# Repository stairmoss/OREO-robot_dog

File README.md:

# OREO – ROS Based Quadruped Robot Dog

# OREO V2 – ROS Powered Vision-Based Quadruped Robot  
### Hack Club Advanced Robotics Project

OREO V2 is a next-generation quadruped robot dog powered by a Raspberry Pi 4 and Teensy microcontroller, upgraded from the original ESP32 version into a full ROS-based intelligent robotic platform.

This version adds:

- 🧠 Computer Vision
- 🐾 12 High-Torque (20kg) Servos
- 🤖 ROS 2 Architecture
- 📡 Behavior-Based Control System
- ❤️ Touch Interaction
- 📷 Person Detection & Following

OREO V2 is no longer just a walking robot — it is an intelligent robotic companion platform built under a constrained $395 budget.

---

# 📌 Project Overview

| Item | Description |
|------|-------------|
| Robot Type | Quadruped (4-legged) |
| Architecture | ROS 2 Modular System |
| Main Computer | Raspberry Pi 4 Model B (4GB) |
| Motor Controller | Teensy Microcontroller |
| Servos per Leg | 3 (Hip, Upper, Knee) |
| Total Servos | 12 × 20kg High Torque |
| Sensors | IMU + Touch Sensor + Camera |
| Frame | 3D Printed Spot Micro Style |
| Power | 2S/3S Li-ion / LiPo Battery |
| Budget | ~$395 USD |
| Difficulty | Intermediate → Advanced |

---

# 🎯 Vision & Purpose

OREO V2 was built to:

- Transition from beginner robotics to ROS-based research structure
- Integrate computer vision into a quadruped platform
- Maintain affordability under strict budget constraints
- Build a modular robotic system expandable to SLAM and AI
- Learn real robotics engineering workflow

This robot is designed as a stepping stone toward advanced robotic systems.

---

# 🧠 System Architecture

OREO V2 uses a layered robotics architecture.

## 🔵 High-Level Control (Raspberry Pi 4)

Runs:

- Ubuntu 22.04 (64-bit)
- ROS 2 Humble
- OpenCV
- Behavior Node
- Gait Controller Node
- Vision Node

Responsibilities:

- Computer vision
- State machine decisions
- Gait generation
- Touch reaction logic
- Serial communication with Teensy

---

## 🟢 Low-Level Control (Teensy)

Responsibilities:

- Servo PWM generation via PCA9685
- Reading IMU data
- Executing joint commands
- Sending feedback (IMU + joint states)

Communication via USB Serial to Raspberry Pi.

---

# 🤖 ROS Node Structure

## 1️⃣ teensy_interface_node
- Converts ROS messages to serial packets
- Publishes:
  - `/joint_states`
  - `/imu`
- Subscribes:
  - `/joint_targets`

---

## 2️⃣ gait_controller_node
- Generates walking/trot gait
- Uses IMU feedback for balance correction
- Publishes `/joint_targets`

---

## 3️⃣ vision_node
- Captures camera feed
- Runs OpenCV person detection
- Publishes:
  - `/person_detected`
  - `/target_direction`

---

## 4️⃣ behavior_node (Robot Brain)

Handles states:

- IDLE
- SEARCH
- FOLLOW
- SIT
- HAPPY
- LOW_BATTERY

Input:
- Vision topic
- Touch topic
- Battery monitoring

Output:
- `/cmd_gait`
- Emotion state commands

---

## 5️⃣ touch_node
Reads capacitive or pressure sensor  
Publishes `/touch_event`  

When touched → Robot enters HAPPY state.

---

# ✨ Features

- 🐕 Full 12 DOF quadruped
- ⚙️ 20kg high torque servos
- 📷 Real-time person detection
- 🚶 Follow-human functionality
- ❤️ Touch-based interaction
- 📐 IMU-based balance correction
- 🔋 Dedicated high-current servo rail
- 🧩 Modular ROS architecture
- 🔌 Teensy real-time motor control
- 🧠 AI-expandable platform

---

# 🧩 Mechanical Design

Based on improved Spot Micro style frame.

## Body
- Central frame housing electronics
- Battery compartment protected
- Ventilation for Raspberry Pi
- Camera mount on head

## Legs
- 3 DOF per leg
- Parallel linkage for better weight distribution
- Reinforced servo mounts for 20kg servos
- Proper torque alignment to reduce mechanical stress

---

# 🔋 Power System

- 2S or 3S Li-ion pack
- High-current BEC or buck converter for servos (6V recommended)
- Separate regulated 5V rail for Raspberry Pi

⚠ Always:
- Measure voltage before connecting servos
- Test load voltage drop
- Never power servos directly from Raspberry Pi

---

# 🛠 Assembly Workflow

## Step 1 – 3D Print Parts
- Body frame
- Leg assemblies (×4)
- Head mount
- Internal mounting brackets

## Step 2 – Mount Servos
- Center all 12 servos before installation
- Attach horns at neutral 90°
- Secure using metal gears and lock screws

## Step 3 – Install Electronics
- Mount Raspberry Pi
- Mount Teensy
- Connect PCA9685
- Connect IMU
- Install touch sensor on head/body

## Step 4 – Wiring
- Servo power rail separated
- Signal wires routed cleanly
- Verify ground common between Teensy & Pi

## Step 5 – Software Setup
- Install Ubuntu on Pi
- Install ROS 2
- Clone project repository
- Build workspace using colcon
- Flash Teensy firmware
- Connect via USB

## Step 6 – Calibration
- Zero joint angles
- Adjust trim offsets
- Test single leg motion
- Test gait without load
- Then test full body

---

# 📦 Bill of Materials (Approx Budget)

| Component | Qty |
|-----------|-----|
| Raspberry Pi 4 (4GB) | 1 |
| Teensy Microcontroller | 1 |
| PCA9685 Servo Driver | 1 |
| 20kg Metal Gear Servos | 12 |
| IMU Sensor | 1 |
| Camera Module | 1 |
| Touch Sensor | 1 |
| Battery Pack | 1 |
| Buck Converter | 1 |
| 3D Printed Parts | 1 Set |
| Screws & Inserts | Set |

Total Estimated Cost: ~$390–395 USD

---

# 🚀 Software Capabilities

Current:

- Basic walk
- Trot gait
- Person detection
- Follow mode
- Touch reaction mode

Future Upgrades:

- SLAM
- Obstacle detection
- AI voice recognition
- Depth camera integration
- Web dashboard control

---

# 🏁 What Makes OREO V2 Special

- Built under strict budget
- Uses ROS (research-level framework)
- Integrates vision and behavior logic
- Maintains affordable hardware
- Fully modular and expandable
- Combines mechanical + electrical + software engineering

OREO V2 is not just a robot dog.

It is a robotics learning platform engineered for serious development while staying budget-conscious.

---

---

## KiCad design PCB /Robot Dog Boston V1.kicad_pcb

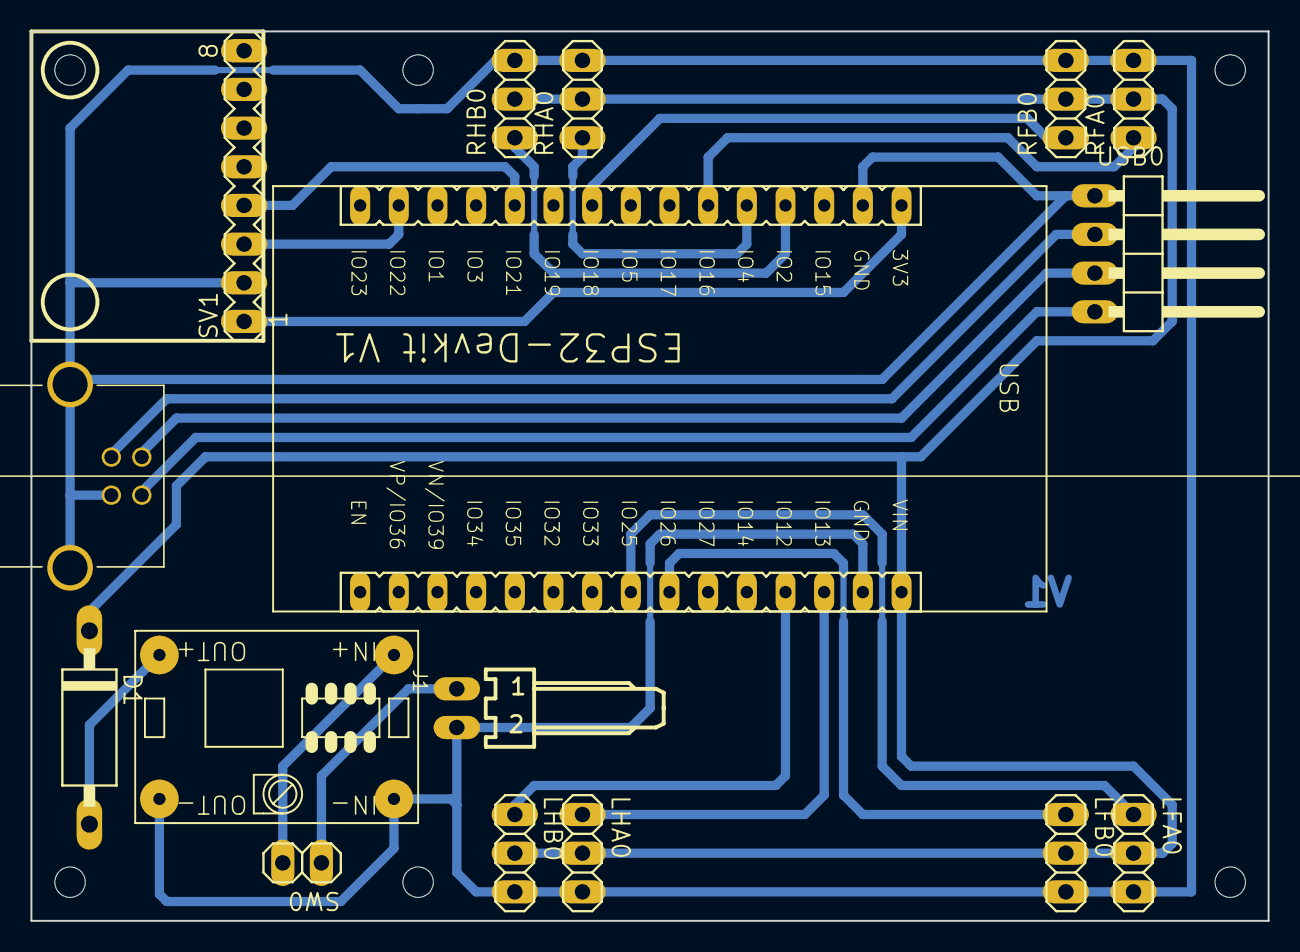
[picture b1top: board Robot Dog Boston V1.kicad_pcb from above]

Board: 2 copper layers, 81.3 x 58.4 mm, 22 parts (0 on the bottom side), 19 nets.

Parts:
D1: 3A; DO15-12
J1: 7.4V; 7395-02
LFA0: 1X03
LFB0: 1X03
LHA0: 1X03
LHB0: 1X03
RFA0: 1X03
RFB0: 1X03
RHA0: 1X03
RHB0: 1X03
SV1: MPU6050; MA08-1
SW0: 1X02
U$1: ESP32DEVKITV1S; ESP32-DEVKIT1S
U$2: REGULATOR_MICRO15.4X9.4; 5V_REGULATOR_BOARD_MICRO_15_4_X_9_4
UNK_HOLE_0: dummyfp0
UNK_HOLE_1: dummyfp1
UNK_HOLE_2: dummyfp2
UNK_HOLE_3: dummyfp3
UNK_HOLE_4: dummyfp4
UNK_HOLE_5: dummyfp5
USB0: 1X04_90
X1: 85-32004-00X

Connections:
+3V3: SV1.1, U$1.3V3
+5V: USB0.4, X1.1
BAT+: J1.1, SW0.1
D+: USB0.2, X1.3
D-: USB0.3, X1.2
GND: J1.2, LFA0.3, LFB0.3, LHA0.3, LHB0.3, RFA0.3, RFB0.3, RHA0.3, RHB0.3, SV1.2, U$1.GND@1, U$1.GND@2, U$2.IN-, U$2.OUT-, USB0.1, X1.4, X1.M1, X1.M2
LFA: LFA0.1, U$1.D25
LFB: LFB0.1, U$1.D26
LHA: LHA0.1, U$1.D13
LHB: LHB0.1, U$1.D12
unnamed: D1.A, U$2.OUT+
RFA: RFA0.1, U$1.D16
RFB: RFB0.1, U$1.D18
RHA: RHA0.1, U$1.D4
RHB: RHB0.1, U$1.D2
SCL: SV1.3, U$1.D22
SDA: SV1.4, U$1.D21
SW: SW0.2, U$2.IN+
VIN: D1.C, LFA0.2, LFB0.2, LHA0.2, LHB0.2, RFA0.2, RFB0.2, RHA0.2, RHB0.2, U$1.VIN

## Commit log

2025-11-14 README.md
2025-12-17 circuit.brd
2025-12-25 Oreo robot dog project
    about the Oreo robot dog project, including design, assembly instructions, and components.
2025-12-25 Replace Hack Club banner and clean up README
    Updated Hack Club banner in README and fixed formatting.
2025-12-25 Add Hack Club logo to README conclusion
    Added Hack Club logo to the conclusion section.
2025-12-25 Add assembly guide for OREO robot dog
    This document provides a comprehensive guide on assembling the OREO robot dog, detailing the tools, parts checklist, and step-by-step instructions for assembly, wiring, and testing.
2025-12-30 Rename servo.ino to code/servo.ino
2026-01-19 Rename HAL.ino to code/HAL.ino
2026-01-19 Rename HAL_ESP32PWM.ino to code/HAL_ESP32PWM.ino
2026-01-19 Rename HAL_PCA9685.ino to code/HAL_PCA9685.ino
2026-01-19 Rename WiFi.ino to code/WiFi.ino
2026-01-19 Rename cli.h to code /cli.h
2026-01-19 Rename cli.ino to code /cli.ino
2026-01-19 Rename cliGet.ino to code /cliGet.ino
2026-01-19 Rename cliSet.ino to code /cliSet.ino
2026-01-19 Rename subscription.h to library/ subscription.h
2026-01-19 Rename config.h to library /config.h
2026-01-19 Rename config_small.h to library /config_small.h
2026-01-19 Rename def.h to library /def.h
2026-01-19 Rename config_wifi.example.h to library /config_wifi.example.h
2026-01-19 Rename cli.h to cli.h
2026-01-19 Rename failsafe.ino to code/failsafe.ino
2026-01-19 Rename gait.ino to code /gait.ino
2026-01-19 Rename helpers.ino to code /helpers.ino
2026-01-19 Rename i2cscan.ino to code /i2cscan.ino
2026-01-19 Rename imu.ino to code /imu.ino
2026-01-19 Rename packagesProcess.ino to code /packagesProcess.ino
2026-01-19 Rename powerSensor.ino to code /powerSensor.ino
2026-01-19 Rename robot_dog_esp32.ino to code /robot_dog_esp32.ino
2026-01-19 Rename settings.ino to code /settings.ino
2026-01-19 Rename subscription.ino to code /subscription.ino
2026-01-19 Rename testHAL.ino to code /testHAL.ino
2026-01-19 Rename webServer.ino to code /webServer.ino
2026-01-19 Rename Robot Dog Boston V1.brd to PCB/Robot Dog Boston V1.brd
2026-01-19 Rename Robot Dog Boston V1.kicad_prl to PCB /Robot Dog Boston V1.kicad_prl
2026-01-19 Rename Robot Dog Boston V1.kicad_pro to PCB /Robot Dog Boston V1.kicad_pro
2026-01-19 Rename Robot Dog Boston V1.sch to PCB /Robot Dog Boston V1.sch
2026-01-19 Revise README for OREO robot dog project
    Updated README to provide detailed project overview, features, assembly instructions, and BOM for the OREO quadruped robot dog.
2026-03-01 Revise README for OREO V2 ROS Quadruped Robot
    Updated project description and specifications for OREO V2, transitioning from ESP32 to ROS-based architecture with enhanced features.
2026-03-01 Rename index.html to stl file /index.html
2026-03-01 Convert BOM to CSV format
    Updated BOM format to use CSV standard with commas.
2026-03-01 Rename model (1).png to 3dpcbmodel.png
2026-03-01 Revise OREO V2 Assembly & Configuration Guide
    Updated assembly guide to focus on hardware assembly and wiring instructions for OREO V2. Revised sections for clarity and added detailed steps for mechanical build and wiring logic.
2026-04-23 Remove Hack Club banner from README
